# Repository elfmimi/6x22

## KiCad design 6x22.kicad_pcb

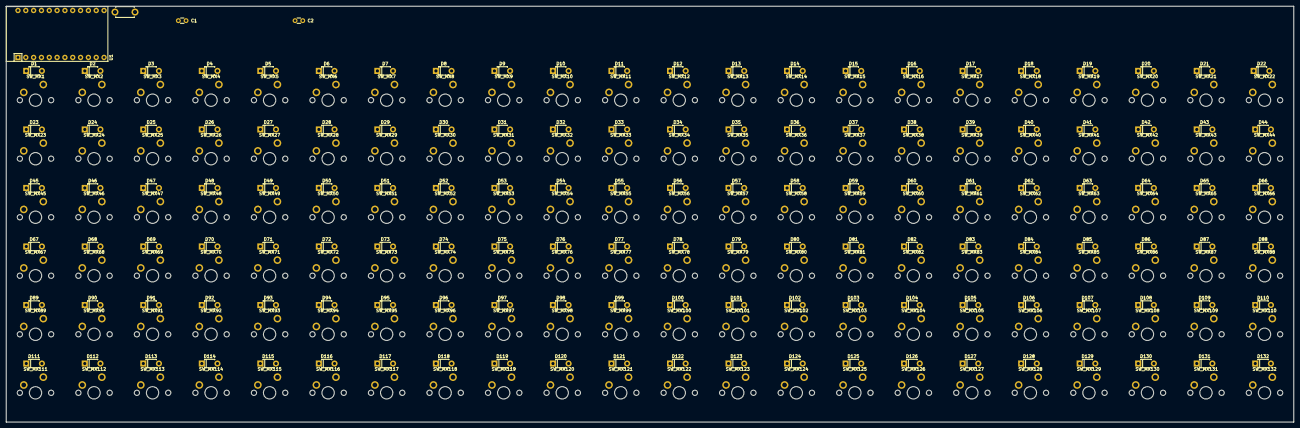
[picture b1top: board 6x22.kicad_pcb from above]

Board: 2 copper layers, 418.0 x 135.0 mm, 268 parts (0 on the bottom side), 152 nets, no tracks yet.

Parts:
C1, C2: 0.1u; C_Disc_D3.0mm_W1.6mm_P2.50mm
D1, D2, D3, D4, D5, D6, D7, D8, D9, D10, D11, D12, D13, D14, D15, D16, D17, D18, D19, D20, D21, D22, D23, D24, D25, D26, D27, D28, D29, D30, D31, D32, D33, D34, D35, D36, D37, D38, D39, D40, D41, D42, D43, D44, D45, D46, D47, D48, D49, D50, D51, D52, D53, D54, D55, D56, D57, D58, D59, D60, D61, D62, D63, D64, D65, D66, D67, D68, D69, D70, D71, D72, D73, D74, D75, D76, D77, D78, D79, D80, D81, D82, D83, D84, D85, D86, D87, D88, D89, D90, D91, D92, D93, D94, D95, D96, D97, D98, D99, D100, D101, D102, D103, D104, D105, D106, D107, D108, D109, D110, D111, D112, D113, D114, D115, D116, D117, D118, D119, D120, D121, D122, D123, D124, D125, D126, D127, D128, D129, D130, D131, D132: 1N4148; D_T-1_P5.08mm_Horizontal
SW1: RESET; TVBP06
SW_MX1, SW_MX2, SW_MX3, SW_MX4, SW_MX5, SW_MX6, SW_MX7, SW_MX8, SW_MX9, SW_MX10, SW_MX11, SW_MX12, SW_MX13, SW_MX14, SW_MX15, SW_MX16, SW_MX17, SW_MX18, SW_MX19, SW_MX20, SW_MX21, SW_MX22, SW_MX23, SW_MX24, SW_MX25, SW_MX26, SW_MX27, SW_MX28, SW_MX29, SW_MX30, SW_MX31, SW_MX32, SW_MX33, SW_MX34, SW_MX35, SW_MX36, SW_MX37, SW_MX38, SW_MX39, SW_MX40, SW_MX41, SW_MX42, SW_MX43, SW_MX44, SW_MX45, SW_MX46, SW_MX47, SW_MX48, SW_MX49, SW_MX50, SW_MX51, SW_MX52, SW_MX53, SW_MX54, SW_MX55, SW_MX56, SW_MX57, SW_MX58, SW_MX59, SW_MX60, SW_MX61, SW_MX62, SW_MX63, SW_MX64, SW_MX65, SW_MX66, SW_MX67, SW_MX68, SW_MX69, SW_MX70, SW_MX71, SW_MX72, SW_MX73, SW_MX74, SW_MX75, SW_MX76, SW_MX77, SW_MX78, SW_MX79, SW_MX80, SW_MX81, SW_MX82, SW_MX83, SW_MX84, SW_MX85, SW_MX86, SW_MX87, SW_MX88, SW_MX89, SW_MX90, SW_MX91, SW_MX92, SW_MX93, SW_MX94, SW_MX95, SW_MX96, SW_MX97, SW_MX98, SW_MX99, SW_MX100, SW_MX101, SW_MX102, SW_MX103, SW_MX104, SW_MX105, SW_MX106, SW_MX107, SW_MX108, SW_MX109, SW_MX110, SW_MX111, SW_MX112, SW_MX113, SW_MX114, SW_MX115, SW_MX116, SW_MX117, SW_MX118, SW_MX119, SW_MX120, SW_MX121, SW_MX122, SW_MX123, SW_MX124, SW_MX125, SW_MX126, SW_MX127, SW_MX128, SW_MX129, SW_MX130, SW_MX131, SW_MX132: SW_Push; SW_Cherry_MX1A_1.00u_PCB
U1: pro_micro; BOARD_Pro_Micro

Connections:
+5V: C1.1, C2.1, U1.21
/COL0: D1.1, D2.1, D3.1, D4.1, D5.1, D6.1, D7.1, D8.1, D9.1, D10.1, D11.1, D12.2, D13.2, D14.2, D15.2, D16.2, D17.2, D18.2, D19.2, D20.2, D21.2, D22.2, U1.11
/COL1: D23.1, D24.1, D25.1, D26.1, D27.1, D28.1, D29.1, D30.1, D31.1, D32.1, D33.1, D34.2, D35.2, D36.2, D37.2, D38.2, D39.2, D40.2, D41.2, D42.2, D43.2, D44.2, U1.12
/COL2: D45.1, D46.1, D47.1, D48.1, D49.1, D50.1, D51.1, D52.1, D53.1, D54.1, D55.1, D56.2, D57.2, D58.2, D59.2, D60.2, D61.2, D62.2, D63.2, D64.2, D65.2, D66.2, U1.13
/COL3: D67.1, D68.1, D69.1, D70.1, D71.1, D72.1, D73.1, D74.1, D75.1, D76.1, D77.1, D78.2, D79.2, D80.2, D81.2, D82.2, D83.2, D84.2, D85.2, D86.2, D87.2, D88.2, U1.14
/COL4: D89.1, D90.1, D91.1, D92.1, D93.1, D94.1, D95.1, D96.1, D97.1, D98.1, D99.1, D100.2, D101.2, D102.2, D103.2, D104.2, D105.2, D106.2, D107.2, D108.2, D109.2, D110.2, U1.15
/COL5: D111.1, D112.1, D113.1, D114.1, D115.1, D116.1, D117.1, D118.1, D119.1, D120.1, D121.1, D122.2, D123.2, D124.2, D125.2, D126.2, D127.2, D128.2, D129.2, D130.2, D131.2, D132.2, U1.16
/ROW0: SW_MX1.1, SW_MX12.1, SW_MX23.1, SW_MX34.1, SW_MX45.1, SW_MX56.1, SW_MX67.1, SW_MX78.1, SW_MX89.1, SW_MX100.1, SW_MX111.1, SW_MX122.1, U1.1
/ROW1: SW_MX2.1, SW_MX13.1, SW_MX24.1, SW_MX35.1, SW_MX46.1, SW_MX57.1, SW_MX68.1, SW_MX79.1, SW_MX90.1, SW_MX101.1, SW_MX112.1, SW_MX123.1, U1.2
/ROW2: SW_MX3.1, SW_MX14.1, SW_MX25.1, SW_MX36.1, SW_MX47.1, SW_MX58.1, SW_MX69.1, SW_MX80.1, SW_MX91.1, SW_MX102.1, SW_MX113.1, SW_MX124.1, U1.5
/ROW3: SW_MX4.1, SW_MX15.1, SW_MX26.1, SW_MX37.1, SW_MX48.1, SW_MX59.1, SW_MX70.1, SW_MX81.1, SW_MX92.1, SW_MX103.1, SW_MX114.1, SW_MX125.1, U1.6
/ROW4: SW_MX5.1, SW_MX16.1, SW_MX27.1, SW_MX38.1, SW_MX49.1, SW_MX60.1, SW_MX71.1, SW_MX82.1, SW_MX93.1, SW_MX104.1, SW_MX115.1, SW_MX126.1, U1.7
/ROW5: SW_MX6.1, SW_MX17.1, SW_MX28.1, SW_MX39.1, SW_MX50.1, SW_MX61.1, SW_MX72.1, SW_MX83.1, SW_MX94.1, SW_MX105.1, SW_MX116.1, SW_MX127.1, U1.8
/ROW6: SW_MX7.1, SW_MX18.1, SW_MX29.1, SW_MX40.1, SW_MX51.1, SW_MX62.1, SW_MX73.1, SW_MX84.1, SW_MX95.1, SW_MX106.1, SW_MX117.1, SW_MX128.1, U1.9
/ROW7: SW_MX8.1, SW_MX19.1, SW_MX30.1, SW_MX41.1, SW_MX52.1, SW_MX63.1, SW_MX74.1, SW_MX85.1, SW_MX96.1, SW_MX107.1, SW_MX118.1, SW_MX129.1, U1.17
/ROW8: SW_MX9.1, SW_MX20.1, SW_MX31.1, SW_MX42.1, SW_MX53.1, SW_MX64.1, SW_MX75.1, SW_MX86.1, SW_MX97.1, SW_MX108.1, SW_MX119.1, SW_MX130.1, U1.18
/ROW9: SW_MX10.1, SW_MX21.1, SW_MX32.1, SW_MX43.1, SW_MX54.1, SW_MX65.1, SW_MX76.1, SW_MX87.1, SW_MX98.1, SW_MX109.1, SW_MX120.1, SW_MX131.1, U1.19
/ROW10: SW_MX11.1, SW_MX22.1, SW_MX33.1, SW_MX44.1, SW_MX55.1, SW_MX66.1, SW_MX77.1, SW_MX88.1, SW_MX99.1, SW_MX110.1, SW_MX121.1, SW_MX132.1, U1.20
GND: C1.2, C2.2, SW1.2, U1.3, U1.4, U1.23
unnamed: D1.2, SW_MX1.2
unnamed: D2.2, SW_MX2.2
unnamed: D3.2, SW_MX3.2
unnamed: D4.2, SW_MX4.2
unnamed: D5.2, SW_MX5.2
unnamed: D6.2, SW_MX6.2
unnamed: D7.2, SW_MX7.2
unnamed: D8.2, SW_MX8.2
unnamed: D9.2, SW_MX9.2
unnamed: D10.2, SW_MX10.2
unnamed: D11.2, SW_MX11.2
unnamed: D12.1, SW_MX12.2
unnamed: D13.1, SW_MX13.2
unnamed: D14.1, SW_MX14.2
unnamed: D15.1, SW_MX15.2
unnamed: D16.1, SW_MX16.2
unnamed: D17.1, SW_MX17.2
unnamed: D18.1, SW_MX18.2
unnamed: D19.1, SW_MX19.2
unnamed: D20.1, SW_MX20.2
unnamed: D21.1, SW_MX21.2
unnamed: D22.1, SW_MX22.2
unnamed: D23.2, SW_MX23.2
unnamed: D24.2, SW_MX24.2
unnamed: D25.2, SW_MX25.2
unnamed: D26.2, SW_MX26.2
unnamed: D27.2, SW_MX27.2
unnamed: D28.2, SW_MX28.2
unnamed: D29.2, SW_MX29.2
unnamed: D30.2, SW_MX30.2
unnamed: D31.2, SW_MX31.2
unnamed: D32.2, SW_MX32.2
unnamed: D33.2, SW_MX33.2
unnamed: D34.1, SW_MX34.2
unnamed: D35.1, SW_MX35.2
unnamed: D36.1, SW_MX36.2
unnamed: D37.1, SW_MX37.2
unnamed: D38.1, SW_MX38.2
unnamed: D39.1, SW_MX39.2
unnamed: D40.1, SW_MX40.2
unnamed: D41.1, SW_MX41.2
unnamed: D42.1, SW_MX42.2
unnamed: D43.1, SW_MX43.2
unnamed: D44.1, SW_MX44.2
unnamed: D45.2, SW_MX45.2
unnamed: D46.2, SW_MX46.2
unnamed: D47.2, SW_MX47.2
unnamed: D48.2, SW_MX48.2
unnamed: D49.2, SW_MX49.2
unnamed: D50.2, SW_MX50.2
unnamed: D51.2, SW_MX51.2
unnamed: D52.2, SW_MX52.2
unnamed: D53.2, SW_MX53.2
unnamed: D54.2, SW_MX54.2
unnamed: D55.2, SW_MX55.2
unnamed: D56.1, SW_MX56.2
unnamed: D57.1, SW_MX57.2
unnamed: D58.1, SW_MX58.2
unnamed: D59.1, SW_MX59.2
unnamed: D60.1, SW_MX60.2
unnamed: D61.1, SW_MX61.2
unnamed: D62.1, SW_MX62.2
unnamed: D63.1, SW_MX63.2
unnamed: D64.1, SW_MX64.2
unnamed: D65.1, SW_MX65.2
unnamed: D66.1, SW_MX66.2
unnamed: D67.2, SW_MX67.2
unnamed: D68.2, SW_MX68.2
unnamed: D69.2, SW_MX69.2
unnamed: D70.2, SW_MX70.2
unnamed: D71.2, SW_MX71.2
unnamed: D72.2, SW_MX72.2
unnamed: D73.2, SW_MX73.2
unnamed: D74.2, SW_MX74.2
unnamed: D75.2, SW_MX75.2
unnamed: D76.2, SW_MX76.2
unnamed: D77.2, SW_MX77.2
unnamed: D78.1, SW_MX78.2
unnamed: D79.1, SW_MX79.2
unnamed: D80.1, SW_MX80.2
unnamed: D81.1, SW_MX81.2
unnamed: D82.1, SW_MX82.2
unnamed: D83.1, SW_MX83.2
unnamed: D84.1, SW_MX84.2
unnamed: D85.1, SW_MX85.2
unnamed: D86.1, SW_MX86.2
unnamed: D87.1, SW_MX87.2
unnamed: D88.1, SW_MX88.2
unnamed: D89.2, SW_MX89.2
unnamed: D90.2, SW_MX90.2
unnamed: D91.2, SW_MX91.2
unnamed: D92.2, SW_MX92.2
unnamed: D93.2, SW_MX93.2
unnamed: D94.2, SW_MX94.2
unnamed: D95.2, SW_MX95.2
unnamed: D96.2, SW_MX96.2
unnamed: D97.2, SW_MX97.2
unnamed: D98.2, SW_MX98.2
unnamed: D99.2, SW_MX99.2
unnamed: D100.1, SW_MX100.2
unnamed: D101.1, SW_MX101.2
unnamed: D102.1, SW_MX102.2
unnamed: D103.1, SW_MX103.2
unnamed: D104.1, SW_MX104.2
unnamed: D105.1, SW_MX105.2
unnamed: D106.1, SW_MX106.2
unnamed: D107.1, SW_MX107.2
unnamed: D108.1, SW_MX108.2
unnamed: D109.1, SW_MX109.2
unnamed: D110.1, SW_MX110.2
unnamed: D111.2, SW_MX111.2
unnamed: D112.2, SW_MX112.2
unnamed: D113.2, SW_MX113.2
unnamed: D114.2, SW_MX114.2
unnamed: D115.2, SW_MX115.2
unnamed: D116.2, SW_MX116.2
unnamed: D117.2, SW_MX117.2
unnamed: D118.2, SW_MX118.2
unnamed: D119.2, SW_MX119.2
unnamed: D120.2, SW_MX120.2
unnamed: D121.2, SW_MX121.2
unnamed: D122.1, SW_MX122.2
unnamed: D123.1, SW_MX123.2
unnamed: D124.1, SW_MX124.2
unnamed: D125.1, SW_MX125.2
unnamed: D126.1, SW_MX126.2
unnamed: D127.1, SW_MX127.2
unnamed: D128.1, SW_MX128.2
unnamed: D129.1, SW_MX129.2
unnamed: D130.1, SW_MX130.2
unnamed: D131.1, SW_MX131.2
unnamed: D132.1, SW_MX132.2
unnamed: SW1.1, U1.22

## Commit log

2019-10-06 6x22 with duplex-matrix
